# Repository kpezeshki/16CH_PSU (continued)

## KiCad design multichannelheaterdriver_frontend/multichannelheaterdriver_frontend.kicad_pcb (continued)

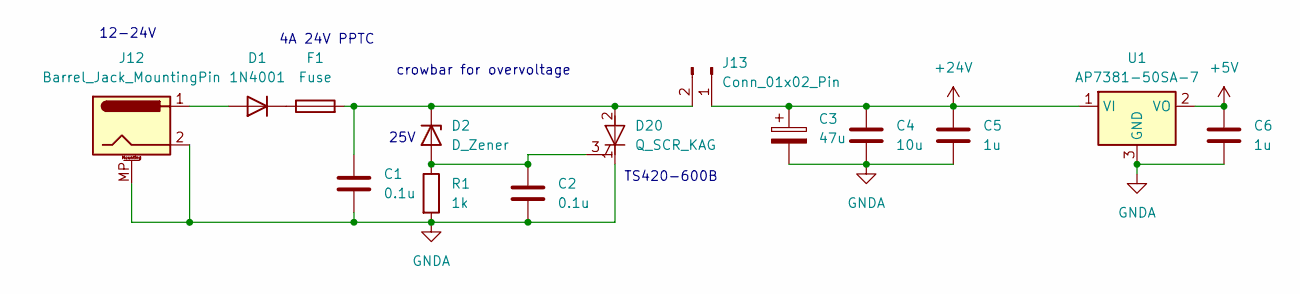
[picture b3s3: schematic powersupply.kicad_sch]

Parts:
C1, C2: 0.1u; C_0603_1608Metric
C3: 47u; CP_Radial_D6.3mm_P2.50mm
C4: 10u; C_0805_2012Metric
C5, C6: 1u; C_0603_1608Metric
D1: 1N4001; D_DO-41_SOD81_P10.16mm_Horizontal
D2: D_Zener; D_SOD-123
D20: Q_SCR_KAG; TO-252-3_TabPin2
F1: Fuse; Fuse_1206_3216Metric
J12: Barrel_Jack_MountingPin; BarrelJack_CUI_PJ-063AH_Horizontal
J13: Conn_01x02_Pin; PinHeader_1x02_P2.54mm_Horizontal
R1: 1k; R_0603_1608Metric
U1: AP7381-50SA-7; SOT-23

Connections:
+5V: C6.1, U1.2 (VO); also elsewhere on the board
+24V: C3.1, C4.1, C5.1, J13.1, U1.1 (VI); also elsewhere on the board
GNDA: C1.2, C2.2, C3.2, C4.2, C5.2, C6.2, D20.1 (K), J12.2, J12.MP (MountPin), R1.2, U1.3 (GND); also elsewhere on the board
unnamed: D1.2 (A), J12.1
unnamed: D1.1 (K), F1.1
unnamed: C2.1, D2.2 (A), D20.3 (G), R1.1
unnamed: C1.1, D2.1 (K), D20.2 (A), F1.2, J13.2

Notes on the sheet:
25V
12-24V
4A 24V PPTC
TS420-600B
crowbar for overvoltage

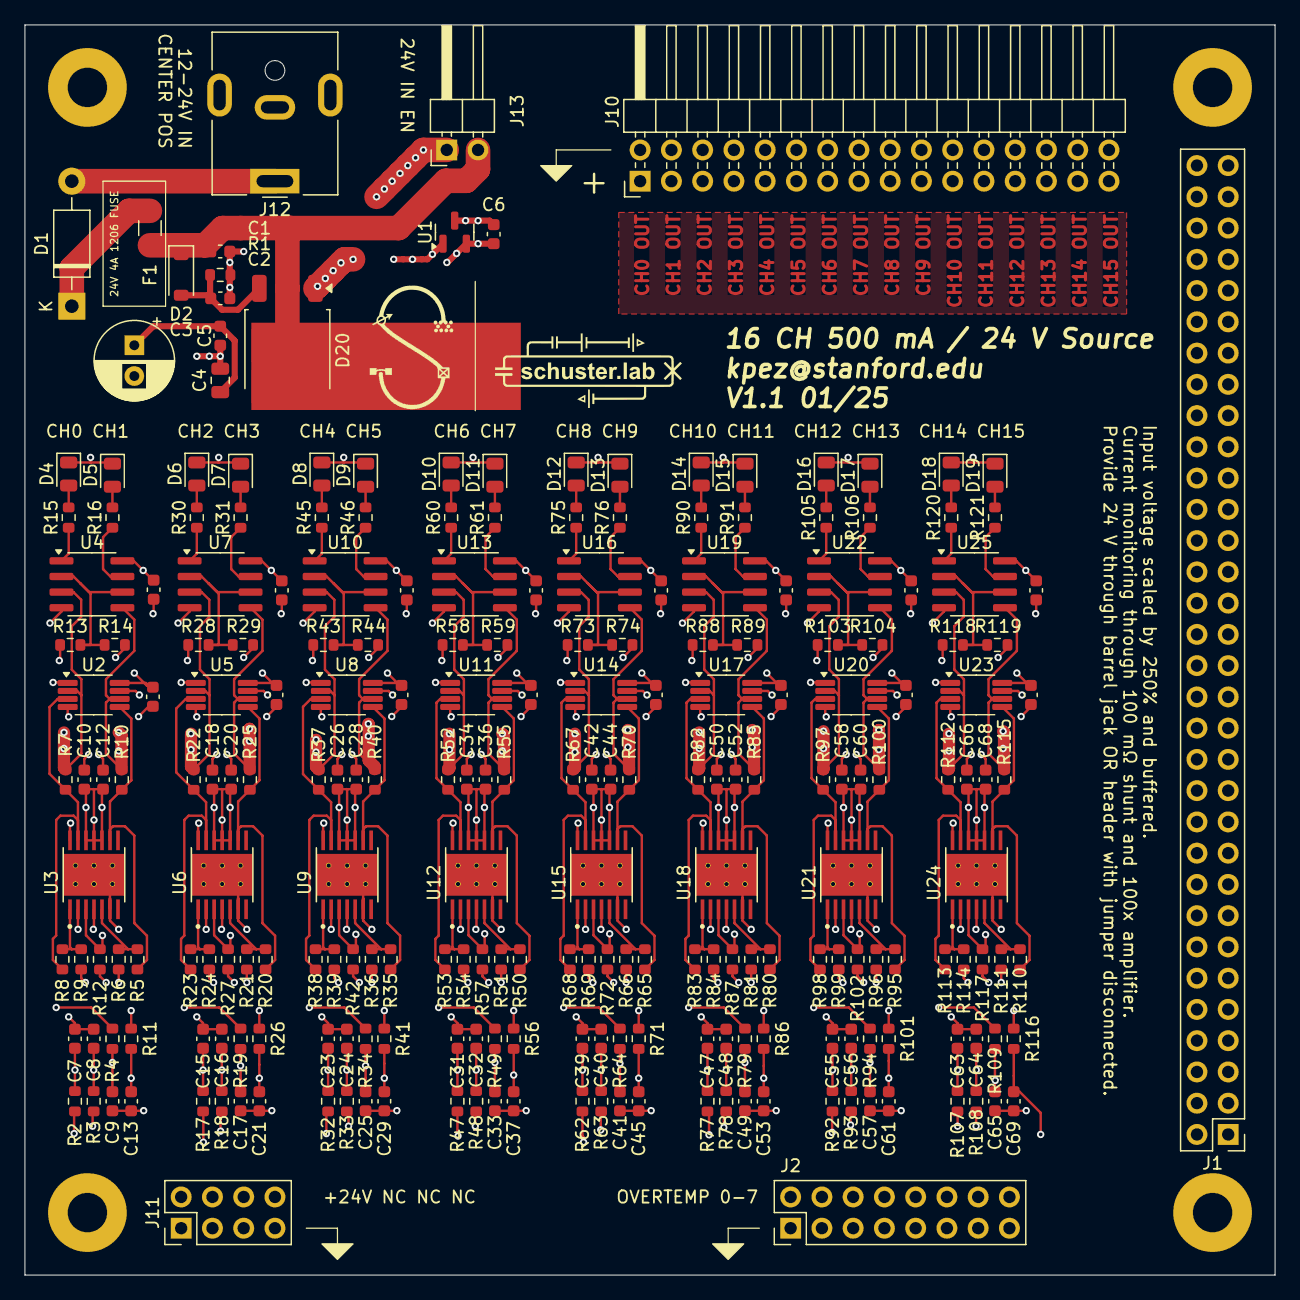
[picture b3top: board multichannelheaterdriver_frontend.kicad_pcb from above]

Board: 6 copper layers, 101.6 x 101.6 mm, 246 parts (0 on the bottom side), 167 nets.

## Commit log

2025-02-13 assorted updates
2025-03-04 added simple host script to sweep bias voltages on a FET RF amplifier
